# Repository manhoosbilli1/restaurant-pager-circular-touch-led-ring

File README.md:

# Restaurant Pager — Circular Touch + LED Ring

ESP32-controlled circular restaurant table pager: a central capacitive **TOUCH** pad surrounded by a 16-LED ring of WS2812B addressable RGBs, plus a **MIC** for audio.

Designed in EasyEDA Pro. Sources here are the **KiCad-converted** form produced by `_backup-tooling/epcb_to_kicad.py` and `_backup-tooling/esch_to_kicad_sch.py`. Original EasyEDA `.epro` archive preserved in `source/` for re-editing.

## At a Glance

- **Board size**: 60 × 60 mm, 4-layer
- **Components**: 101 placed, 17× WS2812B-2020 addressable LEDs forming a ring around a central capacitive touch pad
- **Tracks**: 1,051 (top + bottom)
- **Vias**: 288 (0.305 mm drill / 0.61 mm pad)
- **Copper zones**: 18 (GND + power pours)
- **Schematic**: 200 component instances (101 placed + power/test points), 405 wires
- **Status**: Routed and assembled (manufactured version)

## Renders

3D models for **48 of 101 components** come from the LCSC library (fetched via easyeda2kicad). The ESP32-S3 module, JST-PH connectors, USB-C receptacle, MIC package, and LED bodies are visible with real geometry. The remaining components fall back to flat pad placeholders.

### 3D top (controller side)
The labelled side: PWR / STATUS / 5V / GND / CHG / EXT TOUCH / LED OUT / BAT / VBAT / USB / SPKR / 3V3 / BOOT / RESET test points around the **ESP32-S3 module** (top), JST-PH connectors (left + right), USB-C (bottom right).

### 3D bottom (sensor side)
The user-facing side: central round **TOUCH** pad with a ring of 16 WS2812B-2020 RGB LEDs (real 3D bodies visible), **MIC** package on the side, 4 corner mounting/test pads.

## Schematic

Converted from EasyEDA `.esch` to KiCad 10 `.kicad_sch`. **39 of 44 unique component symbols use real geometry parsed from the EasyEDA `.esym` source files** (matching pin counts, pin positions, body rectangles). The remaining 5 fall back to generic KiCad library symbols.

Also extracted from `.esch`: **154 NET labels** on wire endpoints, **17 global labels** (power rails: 3V3, 5V, GND, VBAT, etc.), **27 no-connect markers**, and **405 wire segments** — preserving the exact connectivity of the original.

Full vector PDF: [board-4/reports/schematic.pdf](board-4/reports/schematic.pdf)

## Files

- `board-4/board4.kicad_pcb` — KiCad 10 PCB layout (converted from `.epcb`)
- `board-4/board4.kicad_sch` — KiCad 10 schematic (converted from `.esch`)
- `board-4/reports/board-3d.png`, `board-3d-back.png` — angled raytraced 3D views
- `board-4/reports/pcb-top.svg`, `pcb-bottom.svg` — copper artwork
- `board-4/reports/schematic.pdf`, `schematic.png` — schematic in PDF + raster
- `board-4/reports/bom.csv` — 101-component BOM with MPN-ish library references (most include LCSC codes)
- `board-4/reports/board-stats.json` — KiCad-computed board statistics
- `source/Restaurant table pager circular.epro` — original EasyEDA Pro project archive
- `source/` also holds the source dump if you re-extract; original lives at the .epro zip

## How this repo was produced

The conversion pipeline lives at `_backup-tooling/` in the parent workspace:

```bash
# 1. PCB conversion (EasyEDA Pro .epcb -> .kicad_pcb)
python epcb_to_kicad.py source/extracted/PCB/<pcb-uuid>.epcb \
    -o board-4/board4.kicad_pcb \
    --footprint-dir source/extracted/FOOTPRINT \
    --project-json source/extracted/project.json \
    --title "Restaurant Pager Circular - Board 4"

# 2. Schematic conversion (EasyEDA Pro .esch -> .kicad_sch, KiCad 10 format)
python esch_to_kicad_sch.py source/extracted/SHEET/<sheet-uuid>/1.esch \
    -o board-4/board4.kicad_sch

# 3. Render artifacts via kicad-cli (3D PNGs, copper SVGs, schematic PDF)
kicad-cli pcb render --rotate -30,0,30 --quality high --floor --perspective \
    -w 1920 -h 1080 --side top -o board-4/reports/board-3d.png board-4/board4.kicad_pcb
kicad-cli sch export pdf -o board-4/reports/schematic.pdf board-4/board4.kicad_sch
```

Schematic emitter patterns are based on [eencyclopedia/lib/kicad/fromEditorState.ts](https://github.com/manhoosbilli1) — a hand-rolled, test-covered KiCad 10 writer.

## Caveats (Phase 1 conversion)

- **101/101 components rendered** on PCB (real pad geometry from `.efoo` library + embedded test-point footprints). Some component rotations or silkscreen positions may be slightly off from the original due to coordinate-frame conventions — this is a known issue in the converter, see `_backup-tooling/epcb_to_kicad.py`.
- **Schematic component symbols** are generic KiCad library placeholders, not full visual replicas of the EasyEDA symbols (would need a per-symbol mapping table).
- **Net connectivity** is preserved at the data level (PAD_NET records → KiCad net IDs) but won't pass DRC/ERC as-is.
- The `.epro` archive in `source/` is the authoritative original — re-import to EasyEDA Pro for any active editing.

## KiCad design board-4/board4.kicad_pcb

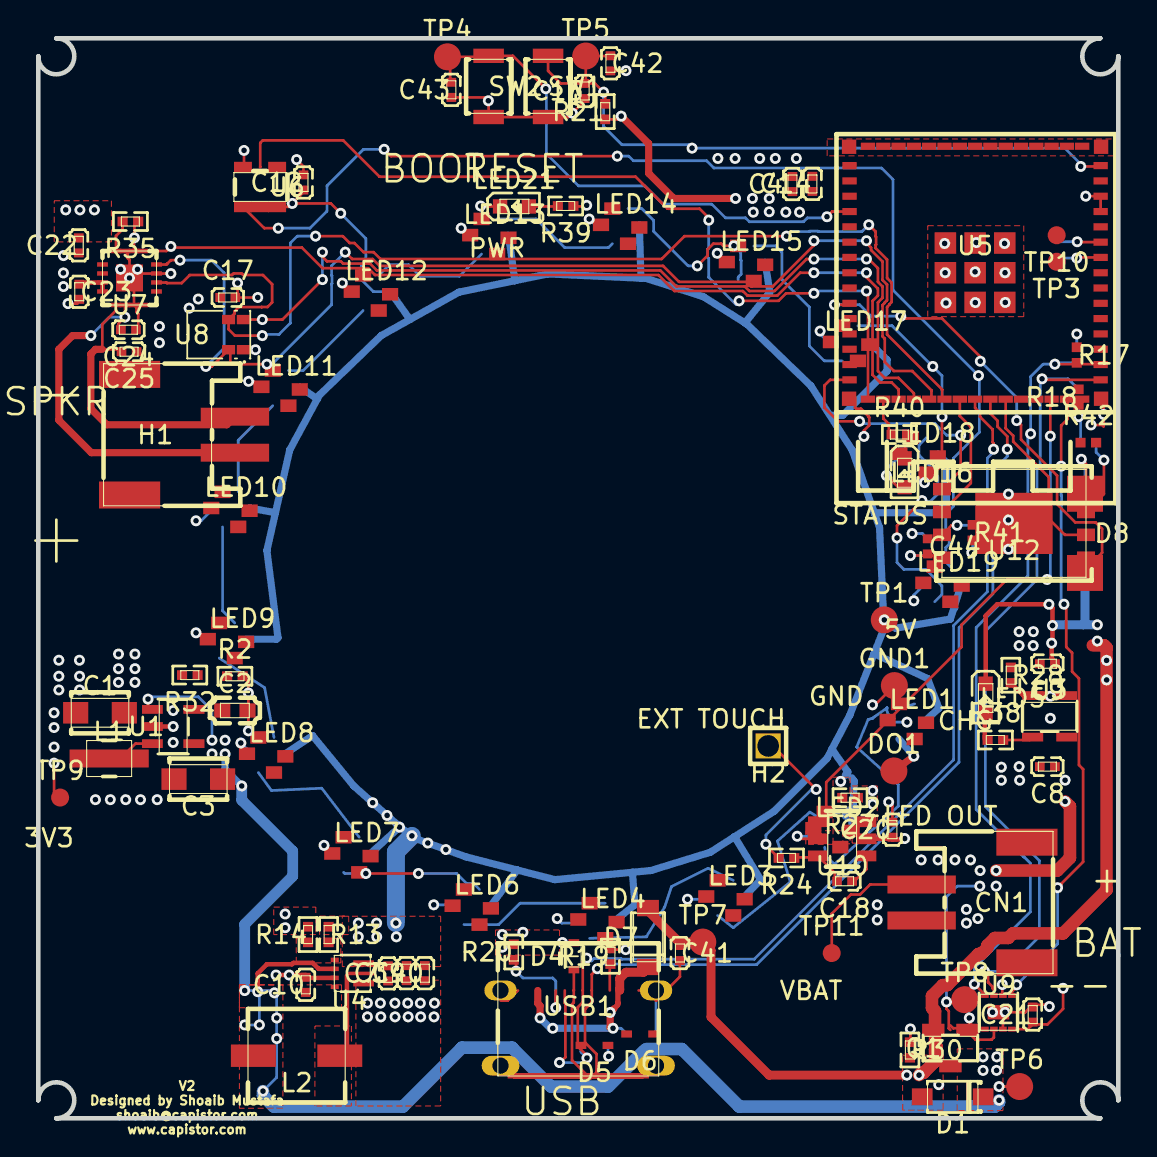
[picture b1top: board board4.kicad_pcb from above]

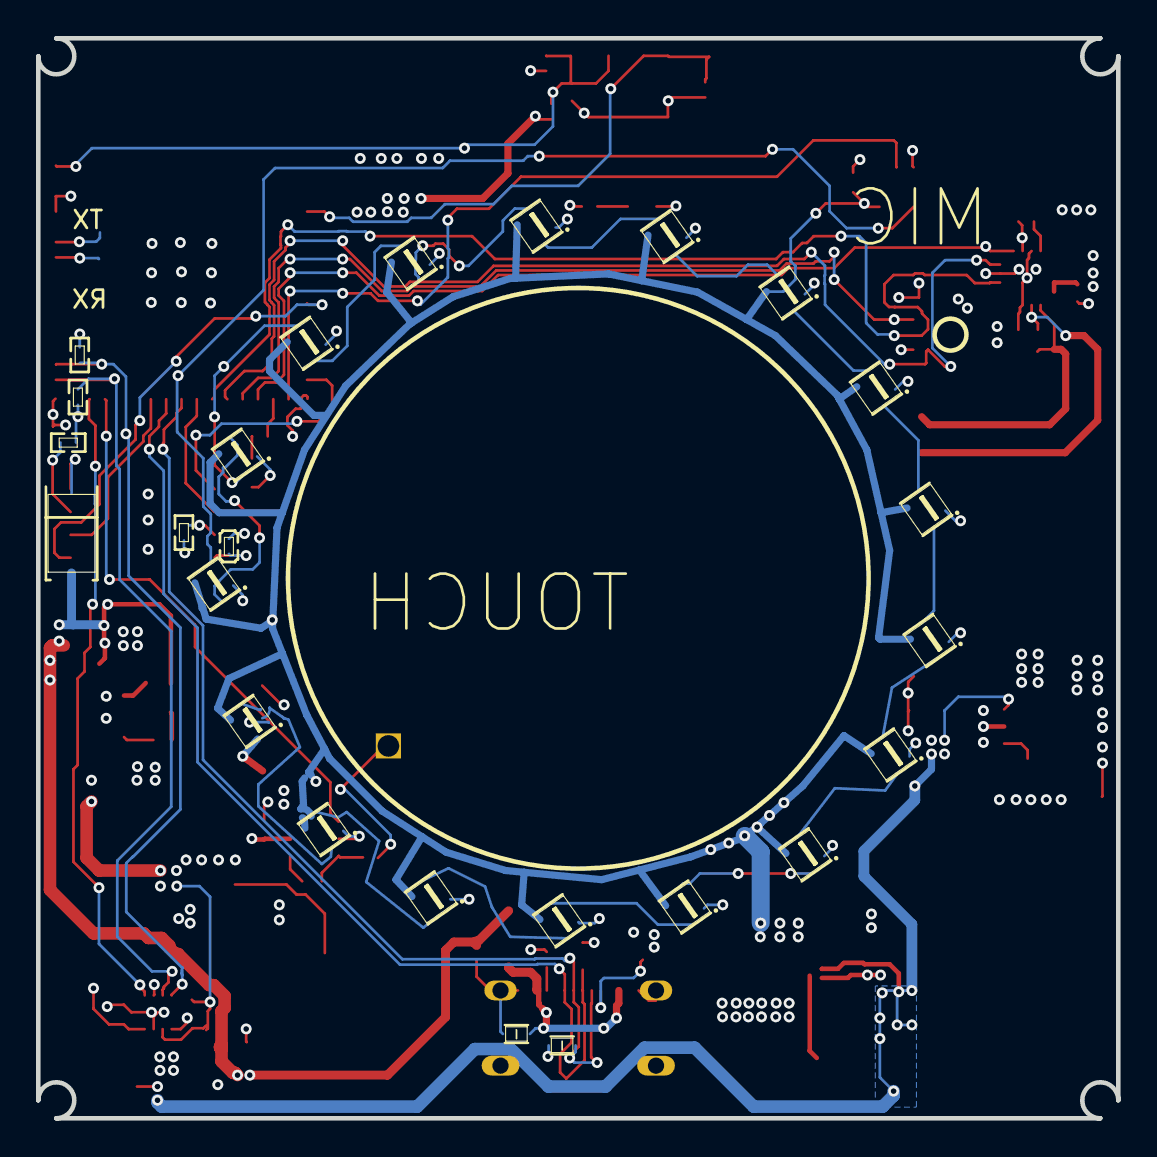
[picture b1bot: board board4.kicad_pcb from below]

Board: 2 copper layers, 60.0 x 60.0 mm, 101 parts (27 on the bottom side), 64 nets.

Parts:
C1, C2, C3, C4, C7, C8, C9, C10, C12, C14, C15, C17, C18, C20, C21, C22, C23, C24, C25, C39, C40, C41, C42, C43, C44: FP
CN1: FP
D1, D4, D5, D6, D7, D8: FP
DO1: Test-Point-0.5mm
GND1: Test-Point-0.5mm
H1, H2: FP
L1, L2: FP
LED1, LED2, LED3, LED4, LED5, LED6, LED7, LED8, LED9, LED10, LED11, LED12, LED13, LED14, LED15, LED16, LED17, LED18, LED19, LED21: FP
Q1: FP
R2, R13, R14, R17, R18, R19, R20, R21, R24, R27, R28, R30, R32, R35, R38, R39, R40, R41, R42: FP
SW1, SW2: FP
TP1, TP3, TP4, TP5, TP6, TP7, TP8, TP9, TP10, TP11: Test-Point-0.5mm
U1, U3, U4, U5, U6, U7, U8, U9, U10, U12: FP
USB1: FP

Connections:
3V3: C1.1, C2.2, C4.2, C14.2, C17.2, C20.2, C21.1, C22.2, C23.2, C44.1, L1.1, R2.2, R17.2, R18.2, R21.2, R27.1, R35.1, R39.1, R41.1, R42.1, TP9.1, U5.3, U7.2, U7.7, U7.8, U8.5, U9.3, U9.9, U10.5, U10.6, U12.8
$1N5324: C18.1, U10.4
$1N5325: C18.2, R24.1, U10.3
$1N5342: R35.2, U7.4
$1N5353: C24.2, H1.2, U7.10
$1N5354: C25.2, H1.1, U7.9
$1N5410: R28.1, U3.5
$1N5412: LED5.1, R38.1
$1N5413: R38.2, U3.1
$1N5423: L1.2, U1.3
$1N5430: L2.1, U4.2
$1N5433: R13.1, R14.2, U4.4
$1N5458: LED18.3, LED19.1
$1N5459: LED17.3, LED18.1
$1N5464: LED15.3, LED17.1
$1N5465: LED14.3, LED15.1
$1N5470: LED13.3, LED14.1
$1N5471: LED12.3, LED13.1
$1N5476: LED11.3, LED12.1
$1N5477: LED10.3, LED11.1
$1N5482: LED9.3, LED10.1
$1N5483: LED8.3, LED9.1
$1N5488: LED7.3, LED8.1
$1N5489: LED6.3, LED7.1
$1N5494: LED4.3, LED6.1
$1N5495: LED3.3, LED4.1
$1N5500: LED2.3, LED3.1
$1N5501: LED1.3, LED2.1
$1N5535: DO1.1, LED1.1
$1N5564: C2.1, R2.1, R32.1, U1.5
$1N5565: D6.2, D7.2, USB1.A4, USB1.A9, USB1.B4, USB1.B9
$1N19227: LED21.2, R39.2
$1N19266: LED16.2, R40.2
$1N28187: R41.2, U12.7
$1N31093: R42.2, U12.3
+5V: C7.1, C12.2, C39.1, C40.1, LED1.4, LED2.4, LED3.4, LED4.4, LED6.4, LED7.4, LED8.4, LED9.4, LED10.4, LED11.4, LED12.4, LED13.4, LED14.4, LED15.4, LED17.4, LED18.4, LED19.4, R13.2, TP1.1, U4.3, U6.5
BM_ALRT: U5.29, U9.5
BOOT: C43.1, SW2.2, TP4.1, U5.4
CC1: R20.2, USB1.A5
CC2: R19.2, USB1.B5
D+: D4.2, U5.24, USB1.A6, USB1.B6
D-: D5.2, U5.23, USB1.A7, USB1.B7
DIN_LED: LED19.3, U6.4
GND: C1.2, C3.2, C4.1, C7.2, C8.2, C9.2, C10.1, C12.1, C14.1, C15.2, C17.1, C20.1, C21.2, C22.1, C23.1, C24.1, C25.1, C39.2, C40.2, C41.1, C42.1, C43.2, C44.2, CN1.1, D4.1, D5.1, D6.1, D8.2, GND1.1, LED1.2, LED2.2, LED3.2, LED4.2, LED6.2, LED7.2, LED8.2, LED9.2, LED10.2, LED11.2, LED12.2, LED13.2, LED14.2, LED15.2, LED16.1, LED17.2, LED18.2, LED19.2, LED21.1, R14.1, R19.1, R20.1, R27.2, R28.2, R30.2, R32.2, SW1.1, SW2.1, U1.2, U3.2, U4.1, U4.6, U5.1, U5.2, U5.42, U5.43, U5.46, U5.47, U5.48, U5.49, U5.50, U5.51, U5.52, U5.53, U5.54, U5.55, U5.56, U5.57, U5.58, U5.59, U5.60, U5.GND, U6.3, U7.3, U7.11, U7.15, U7.17, U9.1, U9.4, U9.6, U10.2, U12.4, U12.9, USB1.1, USB1.A1, USB1.A12, USB1.B1, USB1.B12
LED_BUF: U5.16, U6.2
LED_STATUS: R40.1, U5.17
MIC_CLK: U5.20, U7.16, U8.4
MIC_DATA: U5.19, U8.1
MIC_SELECT: U5.21, U7.14, U8.2
MISO: U5.25, U12.2
MOSI: U5.15, U12.5
RESET: C15.1, C42.2, R21.1, SW1.2, TP5.1, U5.45
RX: TP3.1, U5.39
SCL: R18.1, U5.31, U9.7
SDA: R17.1, U5.32, U9.8
SD_CS: U5.10, U12.1
SD_SCK: U5.22, U12.6
SLC_VCC: C3.1, C10.2, D1.1, L2.2, Q1.2, TP6.1, U1.1, U1.4, U4.5, U4.7
SPKR_DIN: U5.18, U7.1
TOUCH_EXTERNAL: U5.28, U10.1
TOUCH_EXTERNAL_PIN: H2.1, R24.2
TX: TP10.1, U5.40
VBAT: C8.1, CN1.2, Q1.3, TP8.1, TP11.1, U3.3, U9.2
VBUS: C9.1, C41.2, D1.2, D7.1, D8.1, LED5.2, Q1.1, R30.1, TP7.1, U3.4

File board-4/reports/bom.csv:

Designator,LibReference (MPN-ish),Comment/Value,Footprint,Description
C1,CA45-A-16V-10uF-K_C185774,10uF,,
CN1,S2B-PH-SM4-TB(LF)(SN),,,
C2,AC0603JRNPO9BN220,22pF,,
C3,CA45-A-16V-10uF-K_C185774,10uF,,
C4,0402ZD106MAT2A,10uF,,
C7,04026D226MAT2A,22uF,,
C8,0402X475K100NT,4.7uF,,
C9,0402X475K100NT,4.7uF,,
C10,0402ZD106MAT2A,10uF,,
C12,CL05B104KO5NNNC,100nF,,
C14,CL05B104KB54PNC,100nF,,
C15,CL05B104KB54PNC,100nF,,
C17,CT41G-0402-2X1-16V-0.1uF-K(N),100nF,,
C18,CL05B103KB5NNNC,10nF,,
C20,CL05B104KB54PNC,100nF,,
C21,CL05B104KB54PNC,100nF,,
C22,0402ZD106MAT2A,10uF,,
C23,CL05B104KB54PNC,100nF,,
C24,0402N221G500CT,220pF,,
C25,0402N221G500CT,220pF,,
C39,04026D226MAT2A,22uF,,
C40,04026D226MAT2A,22uF,,
C41,0402ZD106MAT2A,10uF,,
C42,CL05A105KP5NNNC,1uF,,
C43,CL05B104KB54PNC,100nF,,
C44,CT41G-0402-2X1-16V-0.1uF-K(N),100nF,,
D1,B5819W_C64885,,,
DO1,Test-Point,,,
D4,LESD5D5.0CT1G_C41399463,,,
D5,LESD5D5.0CT1G_C41399463,,,
D6,LESD5D5.0CT1G_C41399463,,,
D7,1N5819HW-7-F,,,
D8,SMAJ5.0A_C5249616,,,
GND1,Test-Point,,,
H1,S2B-PH-SM4-TB(LF)(SN),,,
H2,HDR-M_2.54_1x1P,,,
L1,FTC252012S2R2MBCA,2.2uH,,
LED1,WS2812B-2020,,,
L2,SLO0520H1R0MTT,1uH,,
LED2,WS2812B-2020,,,
LED3,WS2812B-2020,,,
LED4,WS2812B-2020,,,
LED5,KT-0603R,,,
LED6,WS2812B-2020,,,
LED7,WS2812B-2020,,,
LED8,WS2812B-2020,,,
LED9,WS2812B-2020,,,
LED10,WS2812B-2020,,,
LED11,WS2812B-2020,,,
LED12,WS2812B-2020,,,
LED13,WS2812B-2020,,,
LED14,WS2812B-2020,,,
LED15,WS2812B-2020,,,
LED16,KT-0603R,,,
LED17,WS2812B-2020,,,
LED18,WS2812B-2020,,,
LED19,WS2812B-2020,,,
LED21,KT-0603R,,,
Q1,DMG3415U,,,
R2,RC0402FR-07100KL,,,
R13,AC0402FR-07732KL,,,
R14,CRCW0402100KFKED,,,
R17,0402WGJ0103TCE,,,
R18,0402WGJ0103TCE,,,
R19,RMC04025.1K5%N,,,
R20,RMC04025.1K5%N,,,
R21,0402WGJ0103TCE,,,
R24,SCR0402F10K,,,
R27,SCR0402J0R,,,
R28,RC0402FR-071KL,,,
R30,0402WGJ0103TCE,,,
R32,RC0402FR-0722K1L,,,
R35,0402WGF1004TCE,,,
R38,RT0402FRE07140RL,,,
R39,RT0402FRE07140RL,,,
R40,RT0402FRE07140RL,,,
R41,0402WGJ0103TCE,,,
R42,0402WGJ0103TCE,,,
SW1,B3U-1000P_C231329,,,
SW2,B3U-1000P_C231329,,,
TP1,Test-Point,,,
TP3,Test-Point,,,
TP4,Test-Point,,,
TP5,Test-Point,,,
TP6,Test-Point,,,
TP7,Test-Point,,,
TP8,Test-Point,,,
TP9,Test-Point,,,
TP10,Test-Point,,,
TP11,Test-Point,,,
U1,SY8088IAAC,,,
USB1,USB4105-GF-A,,,
U3,MCP73831T-2ACI/OT,,,
U4,TPS61022RWUR,,,
U5,ESP32-S3-MINI-1-N4R2,,,
U6,SN74LV1T34DBVR_RF v1.0,,,
U7,MAX98357AETE+T,,,
U8,SPH0655LM4H-1-8,,,
U9,MAX17048G+T10,,,
U10,AT42QT1011-TSHR,,,
U12,MX35LF1GE4AB-Z4ITR,,,

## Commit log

2026-05-18 Replace Altium-ASCII parse with full KiCad conversion (PCB + schematic + renders, single board)
2026-05-18 Clean up: remove debug test files
2026-05-18 Remove leftover test/bisect files
2026-05-18 Schematic: use real .esym geometry — 39 of 44 lib_symbols built from EasyEDA source (proper pins, no more red placeholders)
2026-05-19 PCB: negate component rotation to compensate for math/screen frame Y-reflection — LED ring and IC pad orientations now uniform
2026-05-19 Add LCSC component library: 48 components now render with real 3D bodies. Schematic adds 154 NET labels + 17 global labels + 27 no_connects from .esch (was missing).
2026-05-19 PCB: add silk arc handling, restrict SVG export to visible layers (no F.Mask). 3D model rotation kept at 0,0,0 — per-model rotation varies and global offset breaks more than it fixes.
2026-05-19 Schematic: device-table fallback for symbol UUIDs — 44/44 components now use real .esym geometry (was 39/44, the 5 missing had no explicit Symbol attr). Wire endpoints should now land on real pin off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
